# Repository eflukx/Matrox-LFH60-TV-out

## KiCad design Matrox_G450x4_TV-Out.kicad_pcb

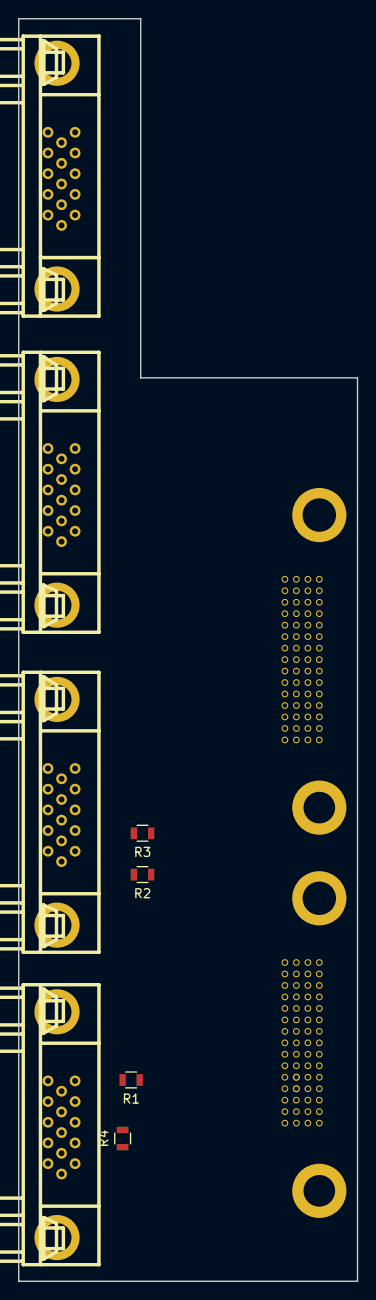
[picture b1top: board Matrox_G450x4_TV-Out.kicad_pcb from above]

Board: 2 copper layers, 37.5 x 139.8 mm, 10 parts (0 on the bottom side), 71 nets, no tracks yet.

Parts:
J1, J1#2: LFH-60; Molex_Matrix_70928_LFH-60_Angled
J2, J2#2, J3, J3#2: DB15_Female_HighDensity; DB_15F-VGA
R1, R2: 75; R_0805
R3, R4: 680; R_0805

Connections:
/BLUE1: J1.35, J1#2.35, J2.3, J2#2.3
/BLUE2: J1.41, J1#2.41, J3.3, J3#2.3
/BLUE_RTN1: J1.26, J1#2.26, J2.8, J2#2.8
/BLUE_RTN2: J1.20, J1#2.20, J3.8, J3#2.8
/COMP_SWITCH1: J1.1, J1#2.1, J2.12, J2#2.12
/COMP_SWITCH2: J1.15, J1#2.15, J3.12, J3#2.12
/GND1: J1.4, J1#2.4, J2.5, J2.10, J2#2.5, J2#2.10
/GND2: J1.12, J1#2.12, J3.5, J3.10, J3#2.5, J3#2.10
/GREEN1: J1.58, J1#2.58, J2.2, J2#2.2
/GREEN2: J1.48, J1#2.48, J3.2, J3#2.2
/GREEN_RTN1: J1.57, J1#2.57, J2.7, J2#2.7
/GREEN_RTN2: J1.49, J1#2.49, J3.7, J3#2.7
/RED1: J1.37, J1#2.37, J2.1, J2#2.1
/RED2: J1.39, J1#2.39, J3.1, J3#2.1
/RED_RTN1: J1.54, J1#2.54, J2.6, J2#2.6
/RED_RTN2: J1.52, J1#2.52, J3.6, J3#2.6
/RGB_SWITCH1: J2.11, J2#2.11, R1.2
/RGB_SWITCH2: J3.11, J3#2.11, R2.2
/RGB_SYNC1: J2.13, J2#2.13, R4.1
/RGB_SYNC2: J3.13, J3#2.13, R3.1
unnamed: J1.2, J1#2.2
unnamed: J1.3, J1#2.3
unnamed: J1.5, J1#2.5, R1.1
unnamed: J1.6, J1#2.6
unnamed: J1.7, J1#2.7
unnamed: J1.8, J1#2.8
unnamed: J1.9, J1.10, J1#2.9, J1#2.10
unnamed: J1.11, J1#2.11, R2.1
unnamed: J1.13, J1#2.13
unnamed: J1.14, J1#2.14
unnamed: J1.16, J1#2.16
unnamed: J1.17, J1#2.17
unnamed: J1.18, J1#2.18
unnamed: J1.19, J1#2.19
unnamed: J1.21, J1#2.21
unnamed: J1.22, J1#2.22
unnamed: J1.23, J1#2.23
unnamed: J1.24, J1#2.24
unnamed: J1.25, J1#2.25
unnamed: J1.27, J1#2.27
unnamed: J1.28, J1#2.28
unnamed: J1.29, J1#2.29
unnamed: J1.30, J1#2.30
unnamed: J1.31, J1#2.31
unnamed: J1.32, J1#2.32
unnamed: J1.33, J1#2.33
unnamed: J1.34, J1#2.34
unnamed: J1.36, J1#2.36
unnamed: J1.38, J1#2.38
unnamed: J1.40, J1#2.40
unnamed: J1.42, J1#2.42
unnamed: J1.43, J1#2.43
unnamed: J1.44, J1#2.44
unnamed: J1.45, J1#2.45
unnamed: J1.46, J1#2.46
unnamed: J1.47, J1#2.47
unnamed: J1.50, J1#2.50, R3.2
unnamed: J1.51, J1#2.51
unnamed: J1.53, J1#2.53
unnamed: J1.55, J1#2.55
unnamed: J1.56, J1#2.56, R4.2
unnamed: J1.59, J1#2.59
unnamed: J1.60, J1#2.60
unnamed: J2.4, J2#2.4
unnamed: J2.9, J2#2.9
unnamed: J2.14, J2#2.14
unnamed: J2.15, J2#2.15
unnamed: J3.4, J3#2.4
unnamed: J3.9, J3#2.9
unnamed: J3.14, J3#2.14
unnamed: J3.15, J3#2.15

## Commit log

2017-08-24 First cut of 2x LFH60 to 4x TV-Out adapter board
